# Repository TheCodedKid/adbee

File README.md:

# adbee

ADB-to-USB adapter. Connect a vintage Apple Desktop Bus keyboard/mouse to a
modern host over USB. A Seeed XIAO ESP32-S3 reads the single-wire ADB bus and
presents itself as a USB HID device.

## BOM

| Ref | Value | Footprint | Qty | Notes |
|-----|-------|-----------|-----|-------|
| M1 | XIAO ESP32-S3 | SeeedStudio_XIAO_ESP32S3 | 1 | MCU module, USB-C |
| J1 | MD-40SM | mini-DIN 4-pin | 1 | CUI, ADB connector |
| Q1 | BSS138 | SOT-23 | 1 | level-shift MOSFET |
| D1 | PESD5V0S1BA | SOD-323 | 1 | TVS ESD diode |
| R1 | 2.2k | 0603 | 1 | bus pull-up |
| R2 | 1k | 0603 | 1 | gate/series |

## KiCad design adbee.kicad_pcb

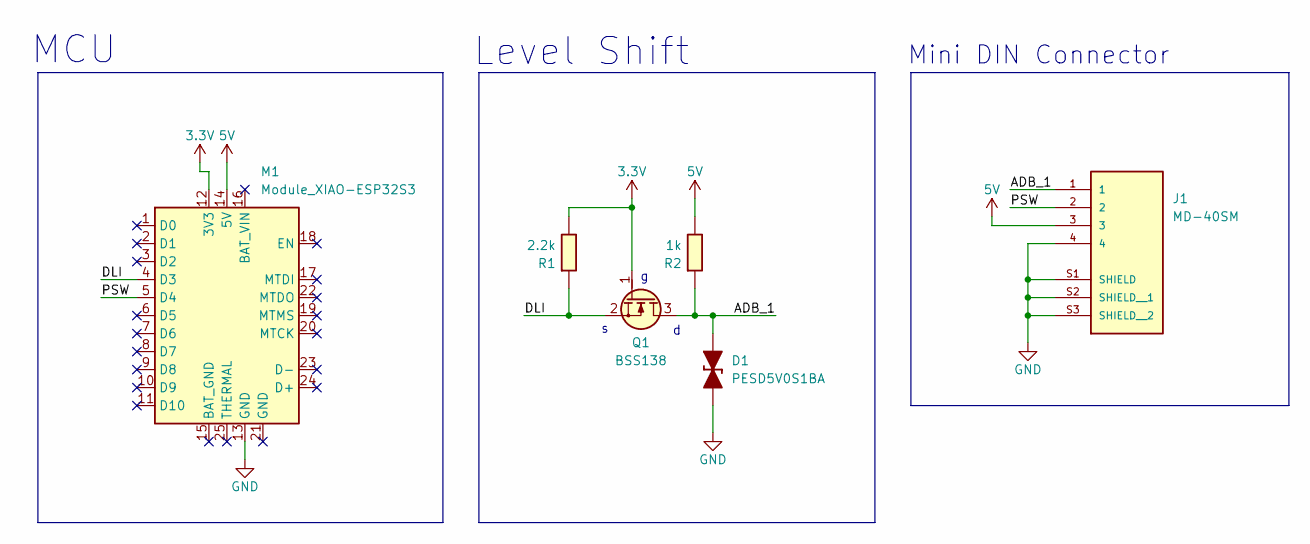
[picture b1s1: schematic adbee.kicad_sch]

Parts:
D1: PESD5V0S1BA; D_SOD-323_TVS
J1: MD-40SM; CUI_MD-40SM; PARTREV 02/18/2022
M1: Module_XIAO-ESP32S3; SeeedStudio_XIAO_ESP32S3
Q1: BSS138; SOT-23
R1: 2.2k; R_0603
R2: 1k; R_0603

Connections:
3.3V: M1.12 (3V3), Q1.1 (G), R1.1
5V: J1.3, M1.14 (5V), R2.1
/ADB_1: D1.2 (A), J1.1, Q1.3 (D), R2.2
/DLI: M1.4 (D3), Q1.2 (S), R1.2
/PSW: J1.2, M1.5 (D4)
GND: D1.1 (K), J1.4, J1.S1 (SHIELD), J1.S2 (SHIELD__1), J1.S3 (SHIELD__2), M1.13 (GND)

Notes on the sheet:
Mini DIN Connector
Level Shift
MCU

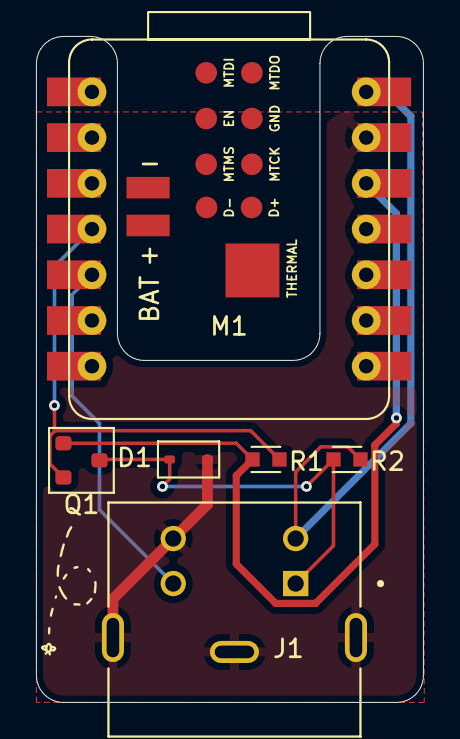
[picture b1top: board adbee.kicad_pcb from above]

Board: 2 copper layers, 21.5 x 37.0 mm, 6 parts (0 on the bottom side), 6 nets.

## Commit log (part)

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2026-06-26 init
2026-06-26 fix folder
2026-06-26 finalizing
